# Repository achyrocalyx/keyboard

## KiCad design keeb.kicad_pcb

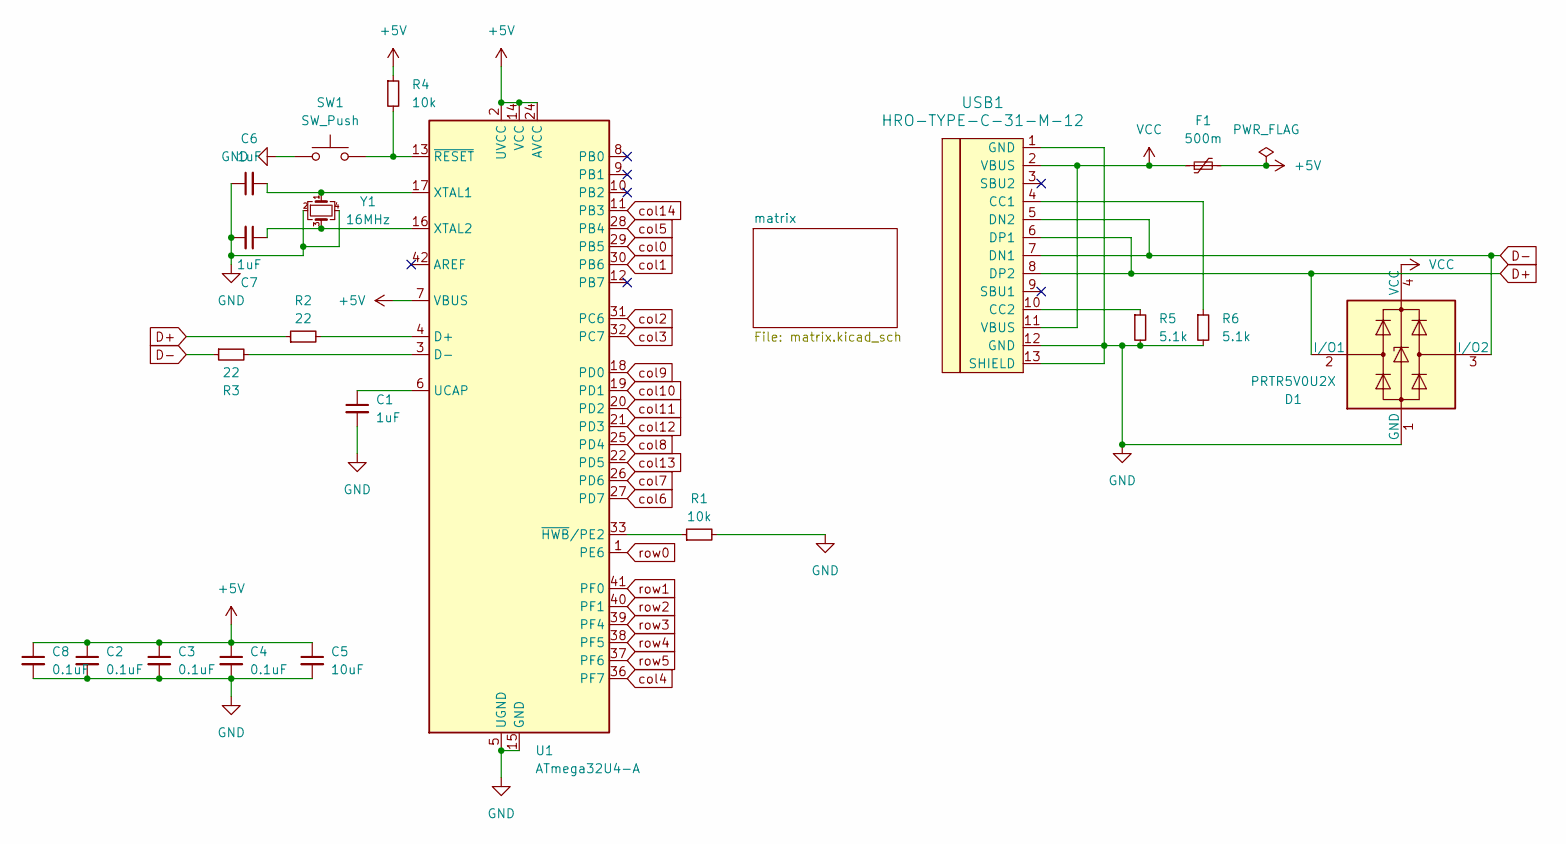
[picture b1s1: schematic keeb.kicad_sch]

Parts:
C1, C6, C7: 1uF; C_0805_2012Metric
C2, C3, C4, C8: 0.1uF; C_0805_2012Metric
C5: 10uF; C_0805_2012Metric
D1: PRTR5V0U2X; SOT-143
F1: 500m; Fuse_1206_3216Metric_Pad1.42x1.75mm_HandSolder
R1, R4: 10k; R_0805_2012Metric
R2, R3: 22; R_0805_2012Metric
R5, R6: 5.1k; R_0805_2012Metric
SW1: SW_Push; SW_SPST_SKQG_WithStem
U1: ATmega32U4-A; TQFP-44_10x10mm_P0.8mm
USB1: HRO-TYPE-C-31-M-12; HRO-TYPE-C-31-M-12-HandSoldering
Y1: 16MHz; Crystal_SMD_3225-4Pin_3.2x2.5mm_HandSoldering

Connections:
+5V: C2.1, C3.1, C4.1, C5.1, C8.1, F1.2, R4.1, U1.2 (UVCC), U1.7 (VBUS), U1.14 (VCC), U1.24 (AVCC), U1.34 (VCC), U1.44 (AVCC)
D+: D1.2 (I/O1), R2.1, USB1.6 (DP1), USB1.8 (DP2)
D-: D1.3 (I/O2), R3.1, USB1.5 (DN2), USB1.7 (DN1)
GND: C1.2, C2.2, C3.2, C4.2, C5.2, C6.1, C7.2, C8.2, D1.1 (GND), R1.2, R5.2, R6.2, SW1.1, U1.5 (UGND), U1.15 (GND), U1.23 (GND), U1.35 (GND), U1.43 (GND), USB1.1 (GND), USB1.12 (GND), USB1.13 (SHIELD), Y1.2, Y1.4
unnamed: R2.2, U1.4 (D+)
unnamed: R3.2, U1.3 (D-)
unnamed: C1.1, U1.6 (UCAP)
unnamed: C6.2, U1.17 (XTAL1), Y1.1
unnamed: C7.1, U1.16 (XTAL2), Y1.3
unnamed: R1.1, U1.33 (~HWB/PE2)
unnamed: R4.2, SW1.2, U1.13 (~RESET)
unnamed: R6.1, USB1.4 (CC1)
unnamed: R5.1, USB1.10 (CC2)
VCC: D1.4 (VCC), F1.1, USB1.2 (VBUS), USB1.11 (VBUS)
col0: U1.29 (PB5); also elsewhere on the board
col1: U1.30 (PB6); also elsewhere on the board
col2: U1.31 (PC6); also elsewhere on the board
col3: U1.32 (PC7); also elsewhere on the board
col4: U1.36 (PF7); also elsewhere on the board
col5: U1.28 (PB4); also elsewhere on the board
col6: U1.27 (PD7); also elsewhere on the board
col7: U1.26 (PD6); also elsewhere on the board
col8: U1.25 (PD4); also elsewhere on the board
col9: U1.18 (PD0); also elsewhere on the board
col10: U1.19 (PD1); also elsewhere on the board
col11: U1.20 (PD2); also elsewhere on the board
col12: U1.21 (PD3); also elsewhere on the board
col13: U1.22 (PD5); also elsewhere on the board
col14: U1.11 (PB3); also elsewhere on the board
row0: U1.1 (PE6); also elsewhere on the board
row1: U1.41 (PF0); also elsewhere on the board
row2: U1.40 (PF1); also elsewhere on the board
row3: U1.39 (PF4); also elsewhere on the board
row4: U1.38 (PF5); also elsewhere on the board
row5: U1.37 (PF6); also elsewhere on the board

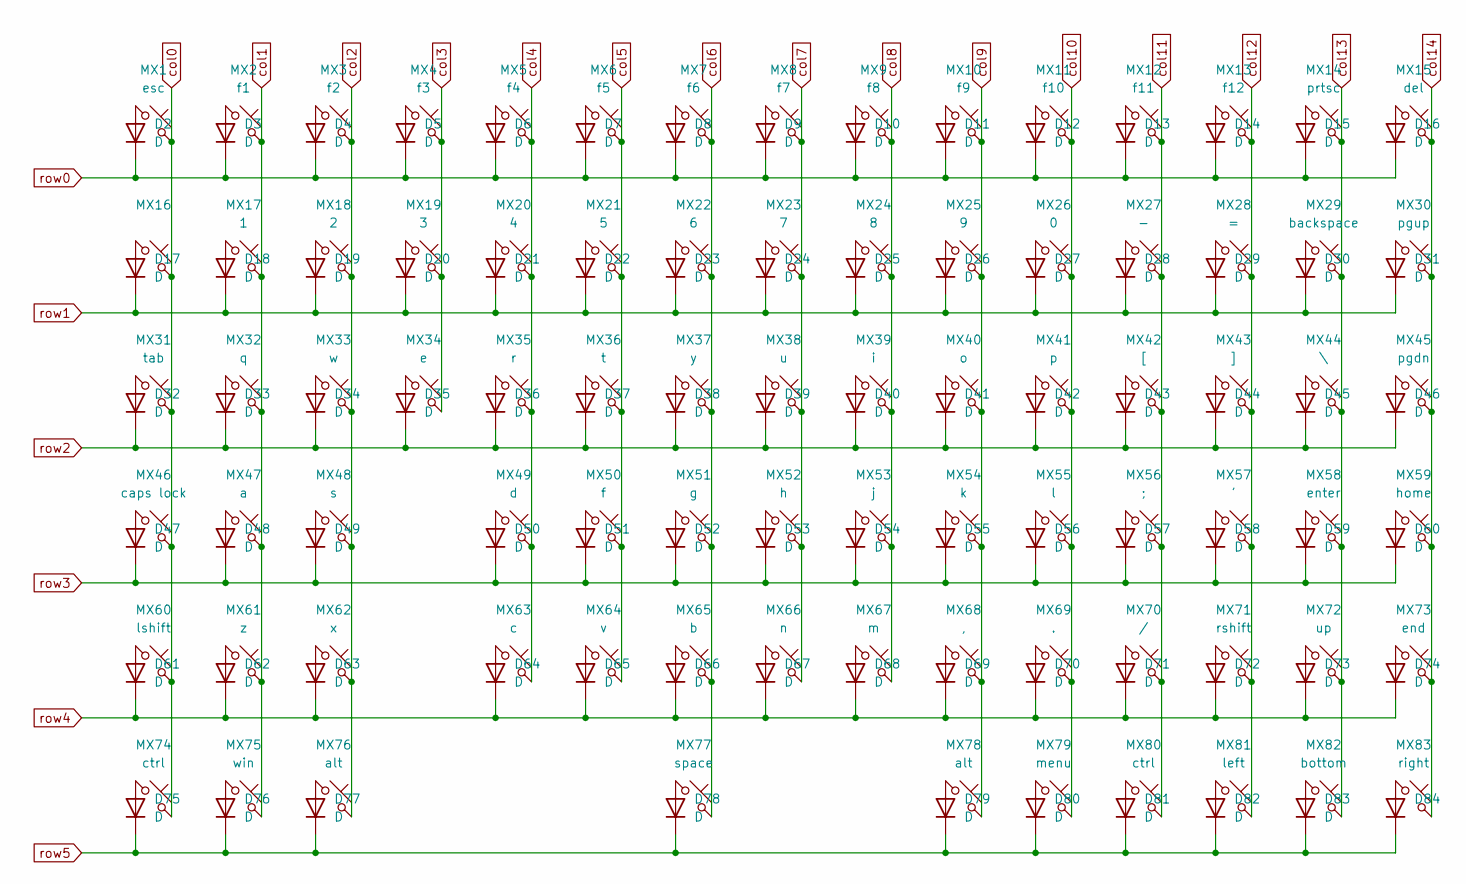
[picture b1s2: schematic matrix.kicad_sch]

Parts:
D2, D3, D4, D5, D6, D7, D8, D9, D10, D11, D12, D13, D14, D15, D16, D17, D18, D19, D20, D21, D22, D23, D24, D25, D26, D27, D28, D29, D30, D31, D32, D33, D34, D35, D36, D37, D38, D39, D40, D41, D42, D43, D44, D45, D46, D47, D48, D49, D50, D51, D52, D53, D54, D55, D56, D57, D58, D59, D60, D61, D62, D63, D64, D65, D66, D67, D68, D69, D70, D71, D72, D73, D74, D75, D76, D77, D78, D79, D80, D81, D82, D83, D84: D; D_SOD-123
MX1: esc; MX-Alps-Hybrid-1U
MX2: f1; MX-Alps-Hybrid-1U
MX3: f2; MX-Alps-Hybrid-1U
MX4: f3; MX-Alps-Hybrid-1U
MX5: f4; MX-Alps-Hybrid-1U
MX6: f5; MX-Alps-Hybrid-1U
MX7: f6; MX-Alps-Hybrid-1U
MX8: f7; MX-Alps-Hybrid-1U
MX9: f8; MX-Alps-Hybrid-1U
MX10: f9; MX-Alps-Hybrid-1U
MX11: f10; MX-Alps-Hybrid-1U
MX12: f11; MX-Alps-Hybrid-1U
MX13: f12; MX-Alps-Hybrid-1U
MX14: prtsc; MX-Alps-Hybrid-1U
MX15: del; MX-Alps-Hybrid-1U
MX16: MX-Alps-Hybrid-1U
MX17: 1; MX-Alps-Hybrid-1U
MX18: 2; MX-Alps-Hybrid-1U
MX19: 3; MX-Alps-Hybrid-1U
MX20: 4; MX-Alps-Hybrid-1U
MX21: 5; MX-Alps-Hybrid-1U
MX22: 6; MX-Alps-Hybrid-1U
MX23: 7; MX-Alps-Hybrid-1U
MX24: 8; MX-Alps-Hybrid-1U
MX25: 9; MX-Alps-Hybrid-1U
MX26: 0; MX-Alps-Hybrid-1U
MX27: -; MX-Alps-Hybrid-1U
MX28: =; MX-Alps-Hybrid-1U
MX29: backspace; MX-Alps-Hybrid-2U-ReversedStabilizers
MX30: pgup; MX-Alps-Hybrid-1U
MX31: tab; MX-Alps-Hybrid-1.5U
MX32: q; MX-Alps-Hybrid-1U
MX33: w; MX-Alps-Hybrid-1U
MX34: e; MX-Alps-Hybrid-1U
MX35: r; MX-Alps-Hybrid-1U
MX36: t; MX-Alps-Hybrid-1U
MX37: y; MX-Alps-Hybrid-1U
MX38: u; MX-Alps-Hybrid-1U
MX39: i; MX-Alps-Hybrid-1U
MX40: o; MX-Alps-Hybrid-1U
MX41: p; MX-Alps-Hybrid-1U
MX42: [; MX-Alps-Hybrid-1U
MX43: ]; MX-Alps-Hybrid-1U
MX44: \; MX-Alps-Hybrid-1.5U
MX45: pgdn; MX-Alps-Hybrid-1U
MX46: caps lock; MX-Alps-Hybrid-1.75U
MX47: a; MX-Alps-Hybrid-1U
MX48: s; MX-Alps-Hybrid-1U
MX49: d; MX-Alps-Hybrid-1U
MX50: f; MX-Alps-Hybrid-1U
MX51: g; MX-Alps-Hybrid-1U
MX52: h; MX-Alps-Hybrid-1U
MX53: j; MX-Alps-Hybrid-1U
MX54: k; MX-Alps-Hybrid-1U
MX55: l; MX-Alps-Hybrid-1U
MX56: ;; MX-Alps-Hybrid-1U
MX57: '; MX-Alps-Hybrid-1U
MX58: enter; MX-Alps-Hybrid-2.25U-ReversedStabilizers
MX59: home; MX-Alps-Hybrid-1U
MX60: lshift; MX-Alps-Hybrid-2.25U-ReversedStabilizers
MX61: z; MX-Alps-Hybrid-1U
MX62: x; MX-Alps-Hybrid-1U
MX63: c; MX-Alps-Hybrid-1U
MX64: v; MX-Alps-Hybrid-1U
MX65: b; MX-Alps-Hybrid-1U
MX66: n; MX-Alps-Hybrid-1U
MX67: m; MX-Alps-Hybrid-1U
MX68: ,; MX-Alps-Hybrid-1U
MX69: .; MX-Alps-Hybrid-1U
MX70: /; MX-Alps-Hybrid-1U
MX71: rshift; MX-Alps-Hybrid-1.75U
MX72: up; MX-Alps-Hybrid-1U
MX73: end; MX-Alps-Hybrid-1U
MX74: ctrl; MX-Alps-Hybrid-1.25U
MX75: win; MX-Alps-Hybrid-1.25U
MX76: alt; MX-Alps-Hybrid-1.25U
MX77: space; MX-Alps-Hybrid-6.25U-ReversedStabilizers
MX78: alt; MX-Alps-Hybrid-1U
MX79: menu; MX-Alps-Hybrid-1U
MX80: ctrl; MX-Alps-Hybrid-1U
MX81: left; MX-Alps-Hybrid-1U
MX82: bottom; MX-Alps-Hybrid-1U
MX83: right; MX-Alps-Hybrid-1U

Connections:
unnamed: D2.2 (A), MX1.1
unnamed: D3.2 (A), MX2.1
unnamed: D4.2 (A), MX3.1
unnamed: D5.2 (A), MX4.1
unnamed: D6.2 (A), MX5.1
unnamed: D7.2 (A), MX6.1
unnamed: D8.2 (A), MX7.1
unnamed: D9.2 (A), MX8.1
unnamed: D10.2 (A), MX9.1
unnamed: D11.2 (A), MX10.1
unnamed: D12.2 (A), MX11.1
unnamed: D13.2 (A), MX12.1
unnamed: D14.2 (A), MX13.1
unnamed: D15.2 (A), MX14.1
unnamed: D16.2 (A), MX15.1
unnamed: D17.2 (A), MX16.1
unnamed: D18.2 (A), MX17.1
unnamed: D19.2 (A), MX18.1
unnamed: D20.2 (A), MX19.1
unnamed: D21.2 (A), MX20.1
unnamed: D22.2 (A), MX21.1
unnamed: D23.2 (A), MX22.1
unnamed: D24.2 (A), MX23.1
unnamed: D25.2 (A), MX24.1
unnamed: D26.2 (A), MX25.1
unnamed: D27.2 (A), MX26.1
unnamed: D28.2 (A), MX27.1
unnamed: D29.2 (A), MX28.1
unnamed: D30.2 (A), MX29.1
unnamed: D31.2 (A), MX30.1
unnamed: D32.2 (A), MX31.1
unnamed: D33.2 (A), MX32.1
unnamed: D34.2 (A), MX33.1
unnamed: D35.2 (A), MX34.1
unnamed: D36.2 (A), MX35.1
unnamed: D37.2 (A), MX36.1
unnamed: D38.2 (A), MX37.1
unnamed: D39.2 (A), MX38.1
unnamed: D40.2 (A), MX39.1
unnamed: D41.2 (A), MX40.1
unnamed: D42.2 (A), MX41.1
unnamed: D43.2 (A), MX42.1
unnamed: D44.2 (A), MX43.1
unnamed: D45.2 (A), MX44.1
unnamed: D46.2 (A), MX45.1
unnamed: D47.2 (A), MX46.1
unnamed: D48.2 (A), MX47.1
unnamed: D49.2 (A), MX48.1
unnamed: D50.2 (A), MX49.1
unnamed: D51.2 (A), MX50.1
unnamed: D52.2 (A), MX51.1
unnamed: D53.2 (A), MX52.1
unnamed: D54.2 (A), MX53.1
unnamed: D55.2 (A), MX54.1
unnamed: D56.2 (A), MX55.1
unnamed: D57.2 (A), MX56.1
unnamed: D58.2 (A), MX57.1
unnamed: D59.2 (A), MX58.1
unnamed: D60.2 (A), MX59.1
unnamed: D61.2 (A), MX60.1
unnamed: D62.2 (A), MX61.1
unnamed: D63.2 (A), MX62.1
unnamed: D64.2 (A), MX63.1
unnamed: D65.2 (A), MX64.1
unnamed: D66.2 (A), MX65.1
unnamed: D67.2 (A), MX66.1
unnamed: D68.2 (A), MX67.1
unnamed: D69.2 (A), MX68.1
unnamed: D70.2 (A), MX69.1
unnamed: D71.2 (A), MX70.1
unnamed: D72.2 (A), MX71.1
unnamed: D73.2 (A), MX72.1
unnamed: D74.2 (A), MX73.1
unnamed: D75.2 (A), MX74.1
unnamed: D76.2 (A), MX75.1
unnamed: D77.2 (A), MX76.1
unnamed: D78.2 (A), MX77.1
unnamed: D79.2 (A), MX78.1
unnamed: D80.2 (A), MX79.1
unnamed: D81.2 (A), MX80.1
unnamed: D82.2 (A), MX81.1
unnamed: D83.2 (A), MX82.1
unnamed: D84.2 (A), MX83.1
col0: MX1.2, MX16.2, MX31.2, MX46.2, MX60.2, MX74.2; also elsewhere on the board
col1: MX2.2, MX17.2, MX32.2, MX47.2, MX61.2, MX75.2; also elsewhere on the board
col2: MX3.2, MX18.2, MX33.2, MX48.2, MX62.2, MX76.2; also elsewhere on the board
col3: MX4.2, MX19.2, MX34.2; also elsewhere on the board
col4: MX5.2, MX20.2, MX35.2, MX49.2, MX63.2; also elsewhere on the board
col5: MX6.2, MX21.2, MX36.2, MX50.2, MX64.2; also elsewhere on the board
col6: MX7.2, MX22.2, MX37.2, MX51.2, MX65.2, MX77.2; also elsewhere on the board
col7: MX8.2, MX23.2, MX38.2, MX52.2, MX66.2; also elsewhere on the board
col8: MX9.2, MX24.2, MX39.2, MX53.2, MX67.2; also elsewhere on the board
col9: MX10.2, MX25.2, MX40.2, MX54.2, MX68.2, MX78.2; also elsewhere on the board
col10: MX11.2, MX26.2, MX41.2, MX55.2, MX69.2, MX79.2; also elsewhere on the board
col11: MX12.2, MX27.2, MX42.2, MX56.2, MX70.2, MX80.2; also elsewhere on the board
col12: MX13.2, MX28.2, MX43.2, MX57.2, MX71.2, MX81.2; also elsewhere on the board
col13: MX14.2, MX29.2, MX44.2, MX58.2, MX72.2, MX82.2; also elsewhere on the board
col14: MX15.2, MX30.2, MX45.2, MX59.2, MX73.2, MX83.2; also elsewhere on the board
row0: D2.1 (K), D3.1 (K), D4.1 (K), D5.1 (K), D6.1 (K), D7.1 (K), D8.1 (K), D9.1 (K), D10.1 (K), D11.1 (K), D12.1 (K), D13.1 (K), D14.1 (K), D15.1 (K), D16.1 (K); also elsewhere on the board
row1: D17.1 (K), D18.1 (K), D19.1 (K), D20.1 (K), D21.1 (K), D22.1 (K), D23.1 (K), D24.1 (K), D25.1 (K), D26.1 (K), D27.1 (K), D28.1 (K), D29.1 (K), D30.1 (K), D31.1 (K); also elsewhere on the board
row2: D32.1 (K), D33.1 (K), D34.1 (K), D35.1 (K), D36.1 (K), D37.1 (K), D38.1 (K), D39.1 (K), D40.1 (K), D41.1 (K), D42.1 (K), D43.1 (K), D44.1 (K), D45.1 (K), D46.1 (K); also elsewhere on the board
row3: D47.1 (K), D48.1 (K), D49.1 (K), D50.1 (K), D51.1 (K), D52.1 (K), D53.1 (K), D54.1 (K), D55.1 (K), D56.1 (K), D57.1 (K), D58.1 (K), D59.1 (K), D60.1 (K); also elsewhere on the board
row4: D61.1 (K), D62.1 (K), D63.1 (K), D64.1 (K), D65.1 (K), D66.1 (K), D67.1 (K), D68.1 (K), D69.1 (K), D70.1 (K), D71.1 (K), D72.1 (K), D73.1 (K), D74.1 (K); also elsewhere on the board
row5: D75.1 (K), D76.1 (K), D77.1 (K), D78.1 (K), D79.1 (K), D80.1 (K), D81.1 (K), D82.1 (K), D83.1 (K), D84.1 (K); also elsewhere on the board

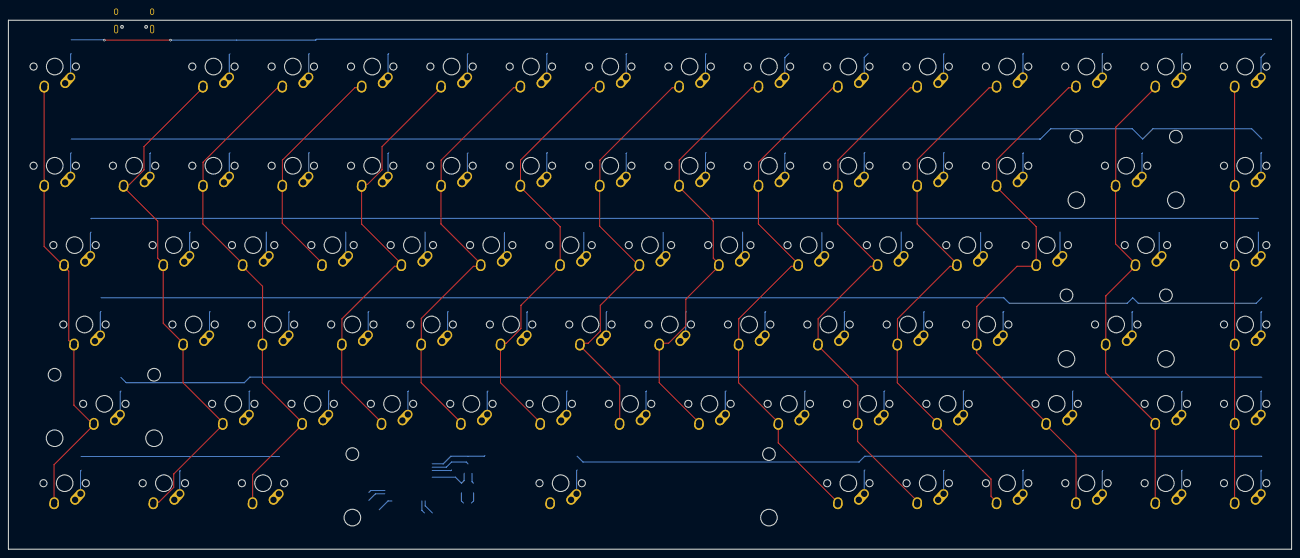
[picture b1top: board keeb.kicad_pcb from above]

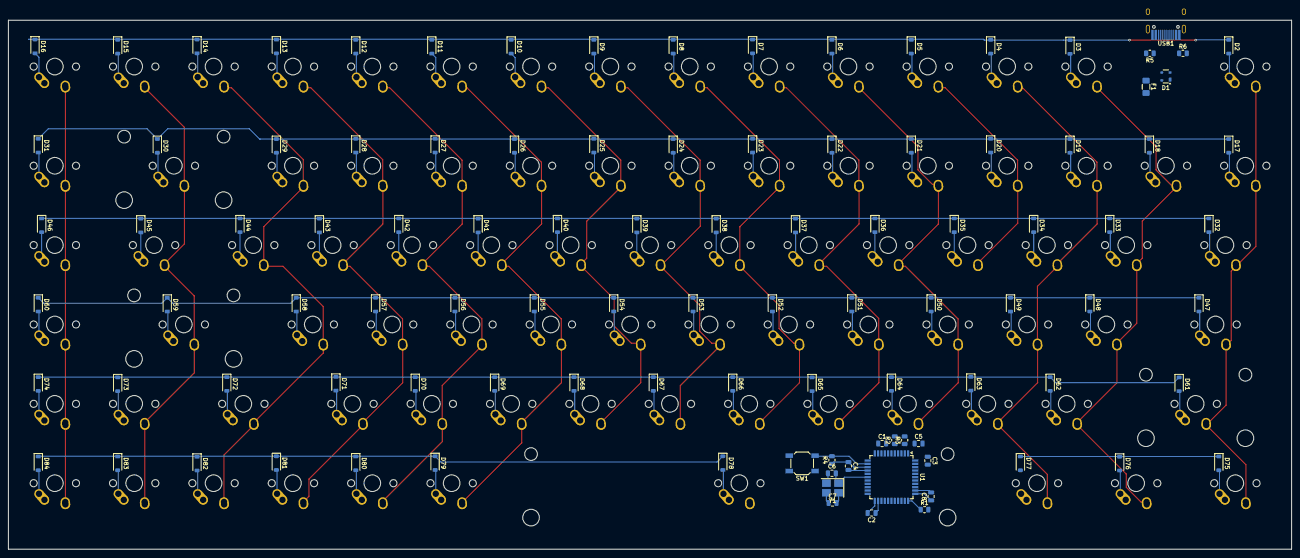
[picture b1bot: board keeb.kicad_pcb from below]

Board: 2 copper layers, 308.0 x 127.0 mm, 186 parts (103 on the bottom side), 118 nets.

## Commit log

2024-07-08 start schematic
    arcade session 1
2024-07-08 actual arcade session 1
2024-07-10 arcade session 2
    usb c and matrix schematic done (with labels)
2024-07-11 arcade session 3
    added footprints; lots of errors :( problem for next time i am free
2024-07-13 arcade session 4(?)
    footprints fixed and components placed/pcb editor settings set up
2024-07-20 arcade session 5
    moving stuff
2024-08-09 fixed mistakes
